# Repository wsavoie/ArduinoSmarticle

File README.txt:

# ArduinoSmarticle
hardware smarticle based around arduino pro mini, and hardware associated with it

***Arduino 1.6.7 must be used
  for some reason the particular servos used do not respond to the servo.h included in the newer arduino versions.

***must download arduinoFFT 1.1.0 for sound smarticle
	can be done from arduino ide, Sketch->include library->manage library  and search for it by name

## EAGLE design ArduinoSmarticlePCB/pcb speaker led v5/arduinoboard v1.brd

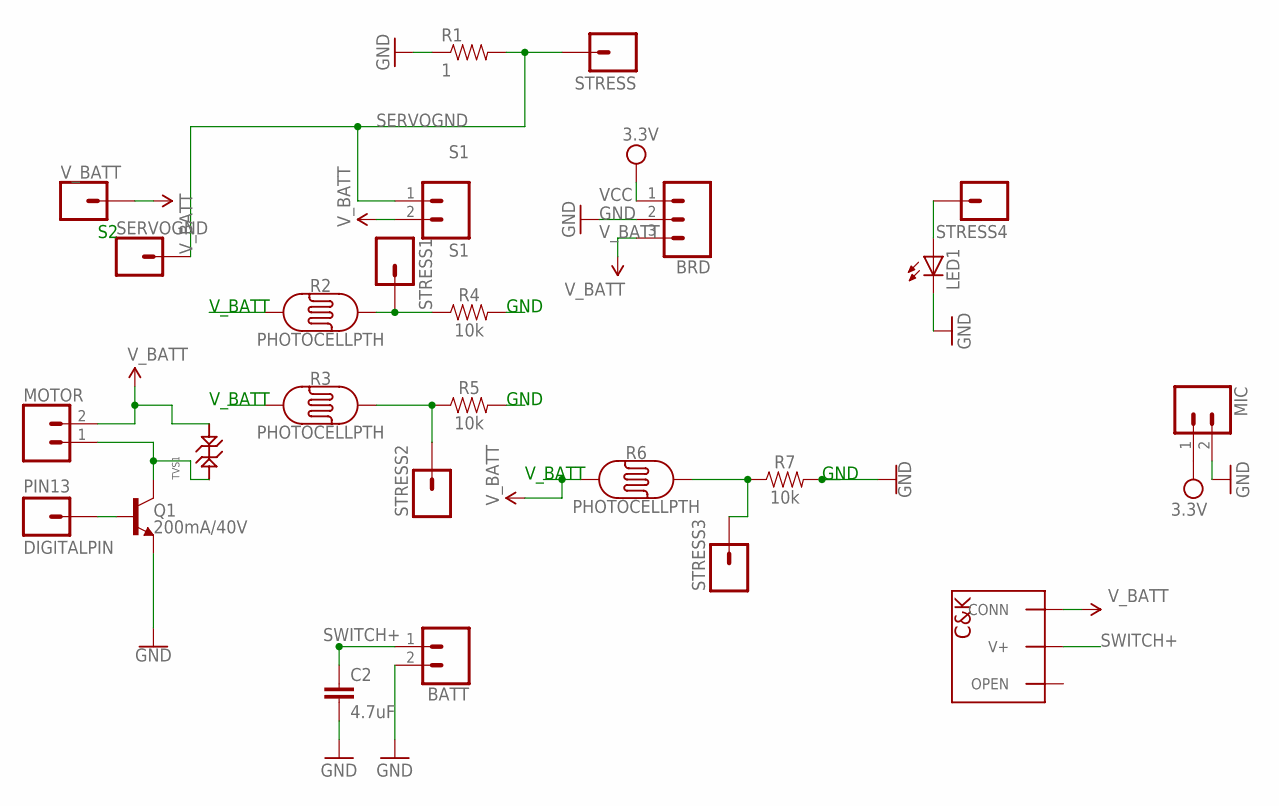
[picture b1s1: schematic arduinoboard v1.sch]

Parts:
BATT: CONN_02; 1X02
BRD: CONN_03; 1X03
C2: 4.7uF; 0603-CAP
LED1: LEDCHIPLED_1206; CHIPLED_1206
MIC: CONN_02; 1X02
MOTOR: CONN_02; 1X02
PIN13: DIGITALPIN; 1X01
Q1: 200mA/40V; TO-92
R1: 1; 0603-RES
R2, R3, R6: PHOTOCELLPTH; PHOTOCELL
R4, R5, R7: 10k; 0603
S1: S1; 1X02
SERVOGND: CONN_01; 1X01
STRESS, STRESS1, STRESS2, STRESS3, STRESS4: M01PTH; 1X01
TVS1: TVS_DIODE_SOD-923; SOD-923
U$1: WILL-BLACKSLIDESWITCH
V_BATT: CONN_01; 1X01

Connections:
GND: BATT.2, BRD.2, C2.2, LED1.C, MIC.2, Q1.1 (E), R1.1, R4.2, R5.2, R7.2
unnamed: R2.2, R4.1, STRESS1.1
unnamed: R3.2, R5.1, STRESS2.1
unnamed: R6.2, R7.1, STRESS3.1
unnamed: PIN13.1, Q1.2 (B)
unnamed: MOTOR.1, Q1.3 (C), TVS1.P$1
unnamed: LED1.A, STRESS4.1
SERVOGND: R1.2, S1.1, SERVOGND.1, STRESS.1
SWITCH+: BATT.1, C2.1, U$1.V+
VCC: BRD.1, MIC.1
V_BATT: BRD.3, MOTOR.2, R2.1, R3.1, R6.1, S1.2, TVS1.P$2, U$1.CONN, V_BATT.1

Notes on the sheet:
GND
V_BATT

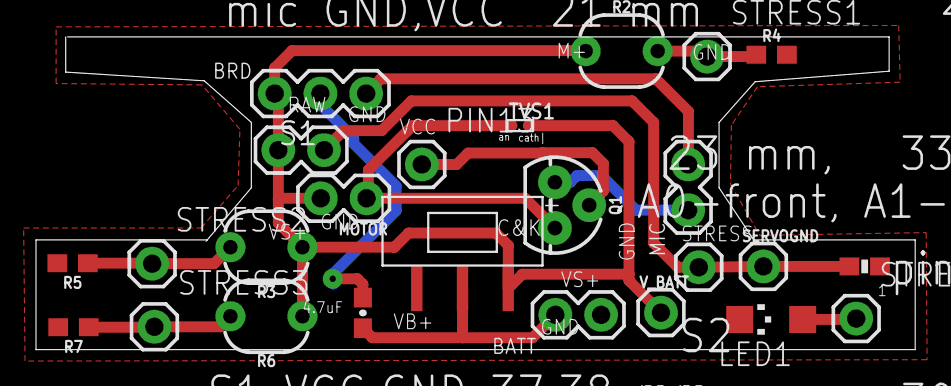
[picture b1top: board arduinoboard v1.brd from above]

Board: 2 copper layers, 48.8 x 17.4 mm, 25 parts (0 on the bottom side), 11 nets.

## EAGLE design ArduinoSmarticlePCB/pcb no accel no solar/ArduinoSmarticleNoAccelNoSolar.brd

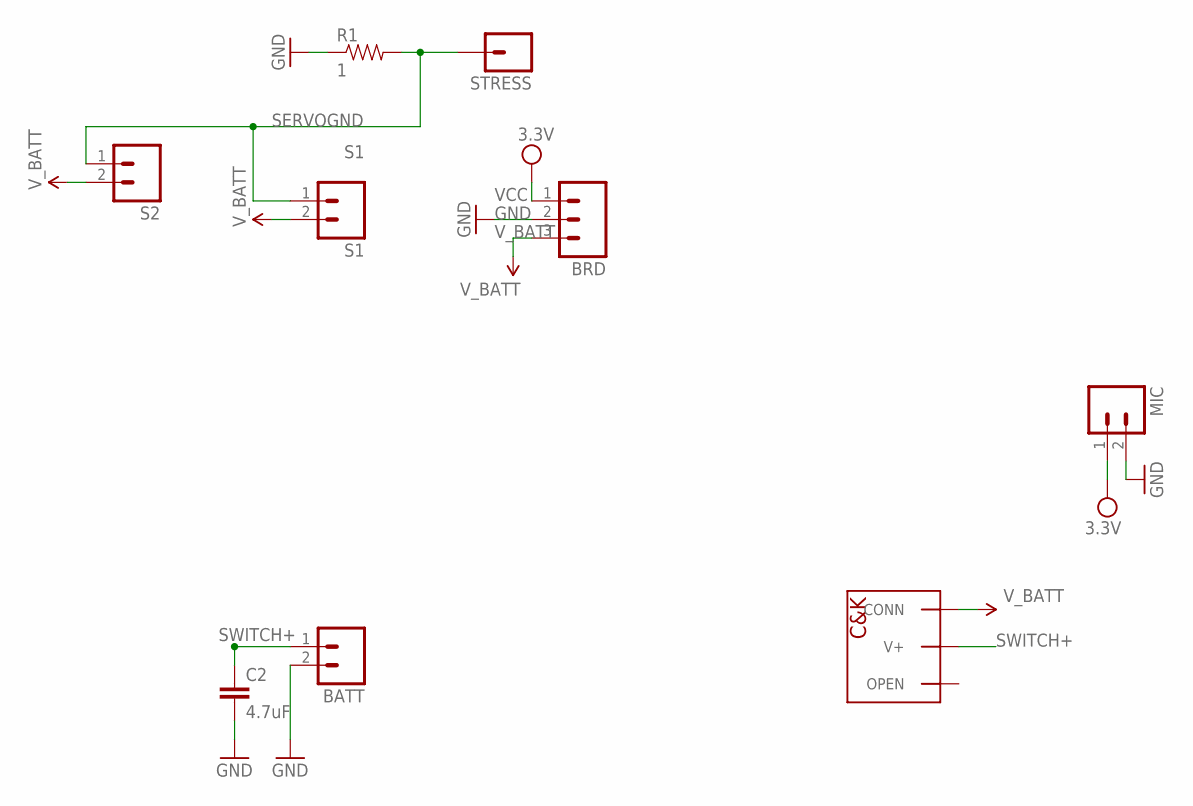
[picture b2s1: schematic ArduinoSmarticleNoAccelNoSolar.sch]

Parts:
BATT: M02PTH; 1X02
BRD: M03PTH; 1X03
C2: 4.7uF; 0603-CAP
MIC: M02PTH; 1X02
R1: 1; 0603-RES
S1: S1; 1X02
S2: M02PTH; 1X02
STRESS: M01PTH; 1X01
U$1: WILL-BLACKSLIDESWITCH

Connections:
GND: BATT.2, BRD.2, C2.2, MIC.2, R1.1
SERVOGND: R1.2, S1.1, S2.1, STRESS.1
SWITCH+: BATT.1, C2.1, U$1.V+
VCC: BRD.1, MIC.1
V_BATT: BRD.3, S1.2, S2.2, U$1.CONN

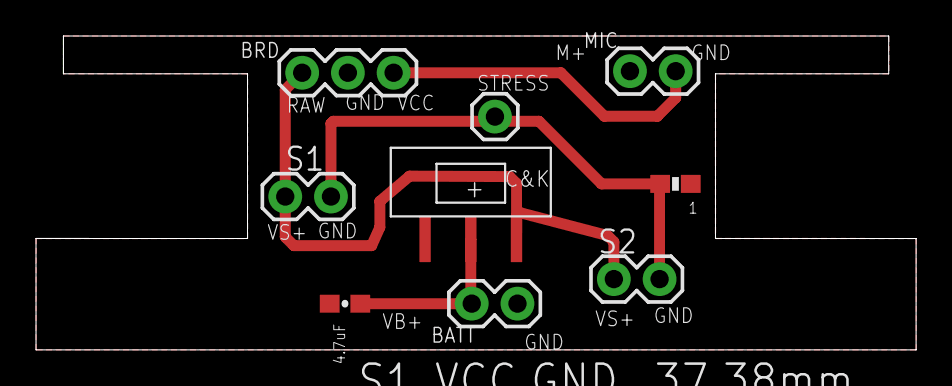
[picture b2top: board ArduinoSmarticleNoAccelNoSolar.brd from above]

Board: 2 copper layers, 48.9 x 17.4 mm, 9 parts (0 on the bottom side), 5 nets.

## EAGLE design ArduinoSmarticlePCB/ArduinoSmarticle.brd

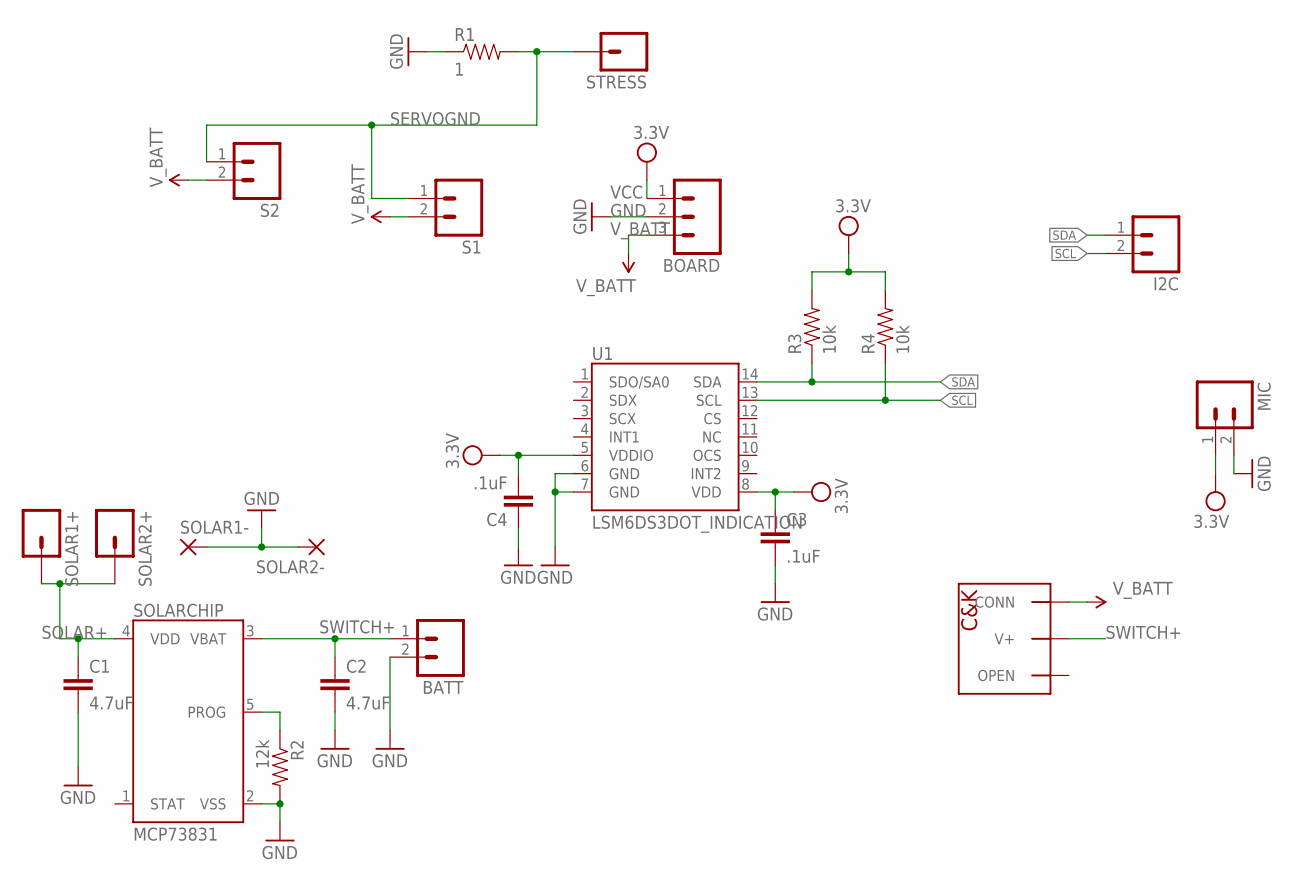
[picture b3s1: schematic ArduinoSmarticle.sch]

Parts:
BATT: M02PTH; 1X02
BOARD: M03PTH; 1X03
C1, C2: 4.7uF; 0603-CAP
C3, C4: .1uF; 0603-CAP
I2C: M02PTH; 1X02
MIC: M02PTH; 1X02
R1: 1; 0603-RES
R2: 12k; 0603
R3, R4: 10k; 0603-RES
S1, S2: M02PTH; 1X02
SOLAR1+, SOLAR2+: M01PTH; 1X01
SOLAR1-, SOLAR2-: 1,6/0,9
SOLARCHIP: MCP73831; SOT23-5
STRESS: M01PTH; 1X01
U1: LSM6DS3DOT_INDICATION; LGA14L_DOT_INDICATOR
U$1: WILL-BLACKSLIDESWITCH

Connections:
GND: BATT.2, BOARD.2, C1.2, C2.2, C3.2, C4.1, MIC.2, R1.1, R2.2, SOLAR1-.1, SOLAR2-.1, SOLARCHIP.2 (VSS), U1.6 (GND), U1.7 (GND)
unnamed 2: U1.12 (CS); also elsewhere on the board
unnamed: R2.1, SOLARCHIP.5 (PROG)
SCL: I2C.2, R4.1, U1.13 (SCL)
SDA: I2C.1, R3.1, U1.14 (SDA)
SERVOGND: R1.2, S1.1, S2.1, STRESS.1
SOLAR+: C1.1, SOLAR1+.1, SOLAR2+.1, SOLARCHIP.4 (VDD)
SWITCH+: BATT.1, C2.1, SOLARCHIP.3 (VBAT), U$1.V+
VCC: BOARD.1, C3.1, C4.2, MIC.1, R3.2, R4.2, U1.1 (SDO/SA0), U1.2 (SDX), U1.3 (SCX), U1.5 (VDDIO), U1.8 (VDD); also elsewhere on the board
V_BATT: BOARD.3, S1.2, S2.2, U$1.CONN

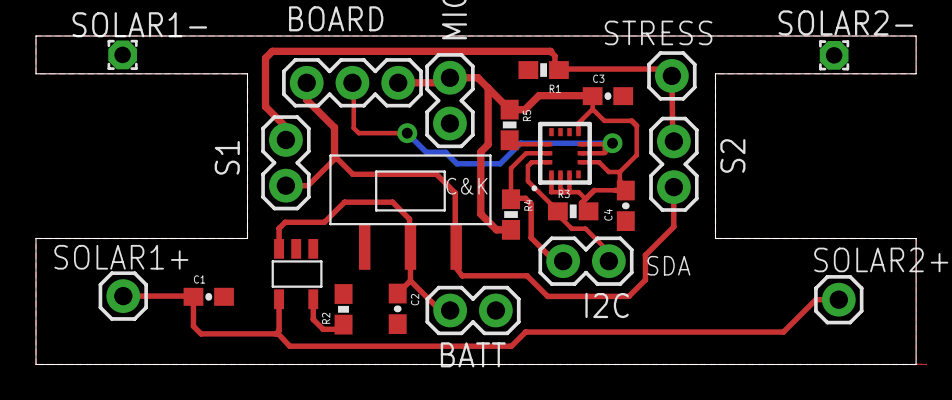
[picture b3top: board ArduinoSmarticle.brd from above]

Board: 2 copper layers, 48.9 x 18.2 mm, 23 parts (0 on the bottom side), 10 nets.

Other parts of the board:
R5: 10k; 0603-RES

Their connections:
unnamed 2: R5.2; also elsewhere on the board
VCC: R5.1; also elsewhere on the board

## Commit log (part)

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2016-01-19 First solidworks file is completed, no tolerances were added.
2016-01-22 final version before wiring up smarticle
2016-01-29 removed all circular references and added case without back
2016-02-02 added spacers to back of case which make servos less mobile
2016-02-10 made clip hole larger on the smarticle case
2016-02-25 added PCB for arduino smarticle
2016-03-23 case 1.5
2016-03-28 fixed some errors in version 1.6
2017-02-27 allows for switching single straight particle with others performing gait
2017-03-23 Added missing initializations
    Also needed to go back to find the AVR035.h file. Now the .ino file
    compiles on my lab machine.
2017-03-27 add old code comment
2017-03-30 Updated photoresist calcs
2017-03-31 needed to delete to get case of filename to be proper
2017-03-31 changed analog pins
2017-04-02 commenting out mean current
2017-04-03 committing extra changes which may have not been saved before committing last time
2017-04-04 Working on the new PR solidworks case
2017-04-07 removed file to replace it in arduinoSmarticle folder in next commit
2017-04-19 Changing the photoresistor gait ranges
2017-05-01 Ross is a silly who got the actions flipped
2017-05-16 added linux version with light thresholds
2017-05-16 Revert "Photoresistors"
2017-05-19 Modifed the light sensing code
    Now based on the maximum light seen over the previous gait period
2017-05-29 made new arduino folder for shea to push the new FFT code
2017-05-29 improved smarticle sound code (edit button value to change frequency played) and added git ignore
2017-05-30 added readme and extra options for .gitignore file
2017-05-30 implemented FFT capability for detecting sound frequency
2017-05-30 changed the code back to previous working version for the light smarticle
2017-05-30 Updated FFT boundary structure and acceptance thresholds
2017-05-31 Fixed frequency boundary computations
2017-05-31 Removed dynamic sampling rate
2017-05-31 Increased inertia for freq detection
2017-06-06 Small changes to formatting
2017-06-19 Added crawling smarticle
2017-06-26 added pcb files with and without the accelerometer and updated solidwork files
2017-06-28 Added forward and backward movement methods
2017-06-30 untested but finished automation code for uno still need to work on the pro mini code
2017-07-03 working before shea implements actual system on plate
2017-07-06 added info about library files necessary to run optitrack code
2017-07-10 testing final versions of crawling automation code
2017-07-11 Fixed automated crawling smarticle gait radius changing
2017-07-12 added println back in and fixed gait radius line, and fixed wrong serial ports
2017-07-13 mini still returns wrong data, need to fix at some point
2017-07-25 casting issue for the smarticle
2017-07-25 can now send info to mini from uno, reset mini to get info from uno
2017-07-26 added code to take 2 min optitrack runs
2017-08-10 cloud smarticle code controlling for even waits between each position is working
2017-08-11 moving files around and cleaning up the repo
2017-08-11 updated the matlab files from changes made on back room computer
2017-08-16 added CMU optitrack program
2017-08-17 added new code which fixes the rigid body relabeling problems for cloud smarticle
2017-08-17 added projection onto y axis from rotated frame plot
2017-08-18 added 1.7 smarticle stl files
2017-09-05 entangled smarticle labview and matlab plotting code
2017-09-05 corrected radius of the ring, increased number of holes, and increased size of holes
2017-09-13 increased isolation size
2017-09-15 Merediths changes to the PCB, now can be milled on the othermill successfully downstairs
2017-09-20 fixing any problems or unclear code from past to get crawling smarticle working
2017-09-20 forgot to stage correct file in last commit
2017-09-22 added new plot types for crawling smarticle
2017-09-27 fixed fft smarticle and updated inputless smarticle
2017-09-28 added 1400hz button
2017-09-29 adding extra plot stuff to prove geometric mech use for this system with diamond gaits and square gaits in crawling smarticle matlab
2017-10-02 improved data collection for smartice cloud and added new plots for cloud data
2017-10-03 small changes to cloud code
2017-10-03 added extra frequency for negative square gait
2017-10-03 cleaned up lightSmart code and added inertia for light sensor
2017-10-04 adding areafraction improvementsd to matlab code
2017-10-06 added other movement sets to cloudSmarticle code
2017-10-09 small changes to parameters
2017-10-12 small variable changes
2017-10-13 creating optimal gait
2017-10-16 updated plotting files for entangledSmarticles
2017-10-23 added working labview serial communication with synced FT data and moved all robcomm files into their own directory
2017-10-24 two matlab scripts which serve as the udp server which trigger optitrack to record from the robot arm computer
2017-11-02 added vibration code
2017-11-02 added previously untracked case without back lightpipe solidworks
2017-11-05 system now properly sends decimal numbers across UDP
2017-11-06 improved plotting code significantly, improved read in of data (both opti and F/T) and hid much of analysis of each file in a separate function
2017-11-07 changed all gaits to for loops in code
2017-11-07 updated labview to accept different filenames and also, added another robot program which waits at end of system (for tightening up)
2017-11-14 made new plots types for easier sorting when trying to plot certain parameters, system now accepts more parameters as well for name
2017-11-14 added some extra structure to entangled file to make clear which system is running
2017-11-15 added extra variables to system and robot arm takes in those values from the labview program
2017-11-19 short function necessary for saving max strain before fracture
2017-11-20 save fracture data in folders containing actual data now
2017-12-01 added matlab files which take in data from the new multi-marker configuration for the entangled system
2017-12-05 added file which has code to fix problems in data files or combines multiple data files together into one
2017-12-06 forgot file in last commit
2017-12-11 added swimming smarticle code for different size diamond gaits and different directions
2017-12-11 improved syncing code between FT sensor and optitrack and fixed index error in ploitting code
2017-12-12 added smarticle swimming data analysis and plotting matlab scripts
2017-12-13 added chord ring solidworks model and info on how it was made
2017-12-13 changed some indices for as data import doesn't read the file the same as it did in earlier versions of matlab (?) made some previous code determine fps from file rather than having it be a magic num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
2018-01-10 added more solidworks chord files and updated chord calculation document
2018-01-11 changed definition of a cycle for many of the plotting methods
2018-01-11 improved nan finding in tracking code
2018-01-17 added filter for integrated path length
2018-01-18 added plotting code for d<s>/dt
2018-01-19 meredith's new pcb version of smarticle with photoresistors
2018-01-22 added powerlaw fitting for cloud data to plotting procedure for ds/dt
2018-01-24 added changes meredith wanted to fit everything inside walker smarticle more easily
2018-01-30 added some relevant files from past work for square gait, and added charging port pin header to solidworks design
2018-02-14 added phi final vs time plot and beginnings of doublet rand amp vs contact cycles code
2018-02-14 added code for comparing SS exp data to zach's SS model data
2018-02-15 added data from zachs mathematica script
2018-02-15 plot ring and active smarticle trajectory together
2018-02-15 slightly altered table with some bad runs removed from dataset
2018-02-22 added extra fitting code for smarticle cloud as well as fixed filtering code
2018-02-26 changed the delay for clouod smarticle system to full size delay
2018-02-27 created variable to track max or min time of all takes
2018-03-02 added stochastic resonance data matrices to add them together
2018-03-29 code to try and characterize how smarticle distances affects volume fraction in cloud
2018-03-29 unsure what the changes are for this commit, after harddrive failure
2018-03-29 changed sampling amount for plotting phi vs t
2018-04-03 added first version of code which moves the nema23 stepper bearing system
2018-04-07 updated zack's model code
2018-04-08 updated sim pars with newest values
2018-04-09 fixed division wrt to T (exp runtime) per shengkais suggestion
2018-04-09 updated solidworks files for the openbuildconnector, it is finally sized correctly
2018-04-12 updated some definitions of and data carried between vis
2018-04-12 improved UDP server communication code for the linear entangled system
2018-04-24 added code for levy flight smarticle system, hasn't been checked yet though
2018-04-24 changed the random amplitude time of the cloud code
2018-04-24 updated matlab scripts to handle analysis and taking of data for the linear bearing entangled system, everything is working
2018-04-24 fixed axes for confinement height on fracture plot and plotting out unit quantity now
2018-04-26 meredith found the final version schematic for the smarticle without vibration motor
2018-05-03 updated optitrack taking script
2018-05-03 added saving and loading of msd data to cloud system
2018-05-08 refactored code and slightly edited plotting code for the ring active particle plot function
2018-05-23 added small changes and bug fixes
2018-06-05 updated all matlab supersmarticle theory code, it is all working now perfectly for xDirection. Will add y-direction later. Added Zack's final updated theory code.
2018-06-05 added new solidworks walking smarticle with female battery connector on back
2018-06-05 added Y mean and variance to expX.mat
2018-06-06 added a parts list with locations where to buy for the smarticles
2018-06-08 re-positioned the text in the file
2018-06-08 updated the parts list for the smarticle adding resistors and capacitors and transistor
2018-06-12 updated solidworks to include the working battery port
2018-06-12 changed fracture vs width plot to linear fraction
2018-06-15 added code which analyzes the strain data for different cycles and evaluates youngs modulus dependency on strain rate and strain for the older robot arm data
2018-06-25 add velocity histogram for supersmarticle
2018-06-25 added 4 new plotting types for cloud data
2018-06-29 fixed the granular temperature calculation
2018-07-05 updated parts list and new version of smarticle with speaker and led
2018-07-13 removed old nan finding method with integrated matlab command
2018-07-13 added many new plotting methods to chain system. Fixed nan assignment with matlab command. updated natnet start record code.
2018-07-16 added jst connector to the parts list
2018-08-03 old matlab files
2018-08-07 added zgait and circle gait
2018-08-09 calibrating clocks via frequency and created wait time calculated from destination position
2018-08-21 added new cloud functions and can read vol frac from certain movies
2018-08-22 updated video tracking working completely
2018-09-04 tracking cloud files
2018-09-05 updated cloud and supersmarticle plotting code
2018-09-05 working interrupt code
2018-09-11 added program to take data for interrupt pin controlled smarticles
2018-10-24 added regular state code to repo
2018-10-24 refactored folder
2018-10-25 added matlab file with strain gauge calibration data
2018-12-06 important name change modifications in trackoptiMulti
2018-12-10 updated variables and methods for labview FT data taking
2019-05-24 added gini plotting function
2019-06-26 added older regular states code

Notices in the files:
parts and their libraries:
SparkFun-Capacitors: Licensing: Creative Commons ShareAlike 4.0 International - https://creativecommons.org/licenses/by-sa/4.0
